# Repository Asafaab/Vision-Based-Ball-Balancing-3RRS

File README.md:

# Vision-Based Ball Balancing Using a 3-RRS Parallel Mechanism

### Mounted on a Differential-Drive Mobile Robot

<p align="center">
  <strong>
    Universidad de Ingeniería y Tecnología (UTEC)
  </strong>
  <br>
  Mechatronics Engineering | Diseño de Sistemas Mecatrónicos
</p>

---

## Digital and Physical Prototype

This project presents a vision-based ball-balancing
system that integrates a three-degree-of-freedom
3-RRS parallel mechanism with a differential-drive
mobile robotic platform.

<table>
<tr>
<th align="center">Digital Prototype</th>
<th align="center">Physical Prototype</th>
</tr>
<tr>
<td width="50%" align="center">

</td>
<td width="50%" align="center">

</td>
</tr>
<tr>
<td align="center">
<em>Autodesk Inventor CAD model</em>
</td>
<td align="center">
<em>Assembled laboratory prototype</em>
</td>
</tr>
</table>

<p align="center">
<b>
Mechanical Design | Computer Vision | Parallel Robotics |
Embedded Control | Power Electronics
</b>
</p>

---

## 1. Project Overview

The project combines a mobile robotic platform
with a **3-RRS Ball-and-Plate parallel mechanism**
designed to regulate the position of a ball
through controlled platform inclination.

The system integrates:

- Differential-drive mobile locomotion.
- A three-limb 3-RRS parallel mechanism.
- Vision-based ball-position estimation.
- A transparent acrylic balancing platform.
- Circular LED illumination.
- Camera-based visual feedback.
- Distributed processing and actuation.
- A dedicated power-distribution PCB.

The mechanical structure was designed and
assembled using Autodesk Inventor and
modular TETRIX components.

### Main Processing Units

**NI myRIO-1900**

- Mobile robot drive control.
- Encoder signal acquisition.
- Inclination measurement.
- Motor control and feedback.

**Raspberry Pi 5**

- Image acquisition and processing.
- Ball-position detection.
- Camera integration.
- Ball-and-Plate actuation.

The vision system uses an Arducam OV9281
global-shutter camera positioned below
the balancing platform.

---

## 2. System Architecture

The robotic platform consists of five
main functional subsystems.

| Subsystem | Description |
|---|---|
| Mobile Robot | Differential-drive TETRIX chassis |
| 3-RRS Mechanism | Parallel balancing platform |
| Vision System | Camera and LED illumination |
| Control System | NI myRIO-1900 and Raspberry Pi 5 |
| Power Distribution | Dedicated PCB and power branches |

### Mobile Robotic Platform

The mobile robot incorporates a modular
aluminum structure, two driven wheels,
and passive omnidirectional support wheels.

The platform provides mechanical support
for the balancing mechanism and its
associated electronics.

### 3-RRS Parallel Mechanism

The balancing mechanism consists of three
servo-actuated limbs connected to a movable
platform through passive links and
spherical joints.

Its configuration allows controlled
platform inclination in roll and pitch.

### Vision System

The vision subsystem incorporates:

- Arducam OV9281 camera module.
- Camera lens and optical filter.
- Camera mounting structure.
- Circular LED illumination.
- Transparent acrylic platform.

### Distributed Control

The NI myRIO-1900 manages the mobile robot
control functions, while the Raspberry Pi 5
handles image processing and balancing
mechanism actuation.

---

## 3. Mechanical Design and CAD Assembly

The mechanical system was developed using
**Autodesk Inventor Professional 2025**.

Native Inventor files and STEP models
are provided for mechanical inspection,
design modification, and interoperability.

### 3.1 Complete Robot Assembly

<p align="center">
<em>
Complete CAD assembly of the differential-drive
robot integrated with the 3-RRS Ball-and-Plate
mechanism.
</em>
</p>

### 3.2 Complete Robot Exploded View

<p align="center">
<em>
Exploded view illustrating the main mechanical
and electronic subsystems of the robotic platform.
</em>
</p>

The exploded assembly highlights:

- Upper structural platform.
- Mobile robot chassis.
- Drive motor assemblies.
- Wheel assemblies.
- Electronic modules.
- 3-RRS balancing mechanism.
- Mechanical supports and interfaces.

### 3.3 3-RRS Mechanism Exploded View

<p align="center">
<em>
Detailed exploded CAD representation of the 3-RRS
Ball-and-Plate mechanism with component
identification and bill of materials.
</em>
</p>

The mechanism includes:

- Transparent acrylic platform.
- Upper structural ring.
- LED ring and supports.
- Spherical joints.
- Passive links.
- Actuated arms.
- Three servomotors.
- Servo mounting structure.
- Camera and optical components.

---

## 4. Vision and LED Illumination System

The vision subsystem is integrated beneath
the transparent acrylic balancing platform.

The circular LED arrangement supports
illumination of the monitored area,
while the camera is mounted below
the platform for visual acquisition.

<p align="center">
<em>
Detailed CAD visualization of the LED ring
and camera optical assembly.
</em>
</p>

### Main Optical Components

| Component | Function |
|---|---|
| Transparent Acrylic Platform | Balancing surface and optical access |
| LED Ring | Illumination of the monitored region |
| Camera Module | Image acquisition |
| Lens Assembly | Optical image formation |
| Optical Filter | Optical filtering |
| Camera Support | Mechanical positioning |

The design includes a dedicated mechanical
arrangement for the camera and its optical
components.

---

## 5. Physical Prototype

The physical prototype was assembled using
a modular TETRIX aluminum chassis.

The balancing mechanism is mounted above
the mobile base, integrating the actuation
system, transparent platform, and
vision-related components.

### Prototype Photographs

<table>
<tr>
<td align="center" width="50%">

<br>
<b>Isometric Overview</b>
</td>
<td align="center" width="50%">

<br>
<b>Front View</b>
</td>
</tr>
<tr>
<td align="center">

<br>
<b>Side View</b>
</td>
<td align="center">

<br>
<b>Power-Switch Detail</b>
</td>
</tr>
</table>

These photographs document the mechanical
integration of the mobile base, balancing
mechanism, wheel assemblies, structural
supports, and electrical wiring.

**Note:** Some CAD configurations represent
design updates and may differ from the
photographed physical prototype.

---

## 6. Power-Distribution PCB

A dedicated power-distribution printed
circuit board was developed for the
robotic platform.

The PCB was designed using **KiCad 9**
and documented for fabrication using
the laboratory CNC manufacturing process.

### PCB 3D Visualization

<p align="center">
<em>
Three-dimensional CAD representation of
the power-distribution PCB.
</em>
</p>

### PCB Specifications

| Parameter | Specification |
|---|---|
| Design Software | KiCad 9 |
| PCB Dimensions | 66.1 x 57.9 mm |
| Board Type | Single-sided |
| Input Supply | 12 V |
| Fabrication | Laboratory CNC |
| Main Function | Power distribution and protection |

The electrical architecture includes
reverse-polarity protection, transient
protection, fused distribution branches,
and auxiliary power connections.

### PCB Design Resources

| Resource | Repository |
|---|---|
| KiCad Source Files | [View files](Power_Distribution_PCB/kicad/) |
| PCB Manufacturing Files | [View files](Power_Distribution_PCB/cnc_L414/) |
| PCB 3D CAD Model | [View files](Power_Distribution_PCB/cad3d/) |
| Electrical Diagrams | [View files](Power_Distribution_PCB/diagramas/) |
| PCB Images | [View files](Power_Distribution_PCB/imagenes/) |
| Thermal Analysis | [View files](Power_Distribution_PCB/termico/) |
| Technical Report | [View PDF](Power_Distribution_PCB/Anexo2_PCB_PDE-DSM_v1.pdf) |
| Pinout and Connections | [View document](Power_Distribution_PCB/Conexiones_y_pines.md) |
| Verification Report | [View document](Power_Distribution_PCB/Informe_verificacion.md) |

For detailed manufacturing requirements
and electrical specifications, consult
the original PCB design documentation.

---

## 7. Engineering Design Resources

The repository provides source files
and technical resources for inspecting,
reproducing, and modifying the platform.

| Design Resource | Format | Repository |
|---|---|---|
| Complete Robot Assembly | STEP | [View](Mechanical_Design/Complete_Robot/Complete_Robot_Assembly.stp) |
| 3-RRS Mechanism | STEP | [View](Mechanical_Design/Complete_Robot/3RRS_Mechanism.stp) |
| Original CAD Package | ZIP | [View](Mechanical_Design/Complete_Robot/Ensamblaje1.zip) |
| Native Inventor Assembly | IAM, IPT, IPJ | [View](Inventor_Source_Files/) |
| Mechanical Drawings | CAD, PDF | [View](Engineering_Drawings/) |
| Kinematic Analysis | MATLAB | [View](Kinematic_Analysis/) |
| CAD Visualizations | PNG | [View](CAD_Visualizations/) |
| Physical Prototype | JPG | [View](Physical_Prototype_Photos/) |
| PCB Design | KiCad, Gerber, STEP | [View](Power_Distribution_PCB/) |

---

## 8. Repository Structure

    Vision-Based-Ball-Balancing-3RRS/
    |
    |-- Mechanical_Design/
    |   `-- Complete_Robot/
    |       |-- Complete_Robot_Assembly.stp
    |       |-- 3RRS_Mechanism.stp
    |       |-- Ensamblaje1.zip
    |       `-- README.md
    |
    |-- Inventor_Source_Files/
    |   |-- DSM_CAD_REPARADO.ipj
    |   |-- Ensamblaje1.iam
    |   |-- Piezas/
    |   |-- Dependencias/
    |   `-- _Verificacion/
    |
    |-- CAD_Visualizations/
    |   |-- Full_Robot_Assembly.png
    |   |-- Full_Robot_Exploded_View.png
    |   |-- 3RRS_Mechanism_Exploded_View.png
    |   |-- Camera_and_LED_System.png
    |   `-- Additional CAD images
    |
    |-- Physical_Prototype_Photos/
    |   `-- Prototype photographs
    |
    |-- Power_Distribution_PCB/
    |   |-- kicad/
    |   |-- cnc_L414/
    |   |-- cad3d/
    |   |-- diagramas/
    |   |-- imagenes/
    |   |-- termico/
    |   `-- Technical documentation
    |
    |-- Engineering_Drawings/
    |   `-- Planos.zip
    |
    |-- Kinematic_Analysis/
    |   `-- Cinemática_RSS.m.txt
    |
    |-- README.md
    `-- LICENSE

---

## 9. Opening the Autodesk Inventor Project

**Required CAD Software:**
Autodesk Inventor Professional 2025.

### Instructions

1. Clone or download the complete repository.
2. Preserve the original directory structure.
3. Open Autodesk Inventor Professional 2025.
4. Activate the project file:

   `Inventor_Source_Files/DSM_CAD_REPARADO.ipj`

5. Open the main assembly:

   `Inventor_Source_Files/Ensamblaje1.iam`

6. Allow Inventor to resolve the referenced
   components and dependencies.
7. Verify the assembly structure and
   mechanical constraints.

The source project includes native Inventor
parts, subassemblies, and supporting
verification records.

### Verification Resources

The verification files are located in:

[Inventor Assembly Verification](Inventor_Source_Files/_Verificacion/)

These records document previous assembly
and reference checks. Users should also
verify the assembly in their local
CAD environment.

---

## 10. Kinematic Analysis

The 3-RRS parallel mechanism is supported
by a MATLAB-based inverse-kinematics model.

The analysis relates the desired platform
orientation to the actuator configuration
through the geometry of the parallel
mechanism.

**Source files:**

[Kinematic Analysis](Kinematic_Analysis/)

The currently published source uses
the `.m.txt` filename extension.

For MATLAB execution, a working copy
can be saved using the `.m` extension.

---

## 11. Design Reproduction Guidelines

For mechanical and electronic reproduction:

1. Review the available CAD models.
2. Inspect the engineering drawings.
3. Verify dimensions and component materials.
4. Check actuator operating limits.
5. Verify mechanical clearances.
6. Inspect the PCB connection diagrams.
7. Review electrical protection requirements.
8. Validate the assembly before operation.

CAD visualizations represent the
documented design configurations.

Physical prototype photographs document
the hardware arrangement shown at the
time of acquisition.

---

## 12. Original Project and Acknowledgments

The 3-RRS Ball-and-Plate mechanism was adapted
from the open-source Ball-Balancing-Robot
project developed by **I-M-Robotics-Lab**.

Original repository:

[Ball-Balancing-Robot — I-M-Robotics-Lab](https://github.com/I-M-Robotics-Lab/Ball-Balancing-Robot)

The present work integrates the mechanism
with a differential-drive mobile robot,
vision hardware, distributed control,
and a dedicated power-distribution PCB.

The original design attribution and
applicable licensing conditions are preserved.

---

## 13. License

This repository includes the
**GNU General Public License v3.0**.

See the [LICENSE](LICENSE) file
for the complete license text.

Third-party components and reused
resources remain subject to their
respective licensing and attribution
requirements.

---

## 14. Project Information

**Project Title:**

Vision-Based Ball Balancing Using a 3-RRS
Parallel Mechanism Mounted on a
Differential-Drive Mobile Robot.

**Institution:**
Universidad de Ingeniería y Tecnología (UTEC).

**Location:**
Lima, Peru.

**Course:**
Diseño de Sistemas Mecatrónicos (DSM).

**Mechanical CAD:**
Autodesk Inventor Professional 2025.

**Electronic Design:**
KiCad 9.

**Engineering Analysis:**
MATLAB.

**Computing Platforms:**
NI myRIO-1900 and Raspberry Pi 5.

**Repository Contents:**
Mechanical CAD, PCB design, engineering
drawings, kinematic analysis, CAD visualizations,
and physical prototype documentation.

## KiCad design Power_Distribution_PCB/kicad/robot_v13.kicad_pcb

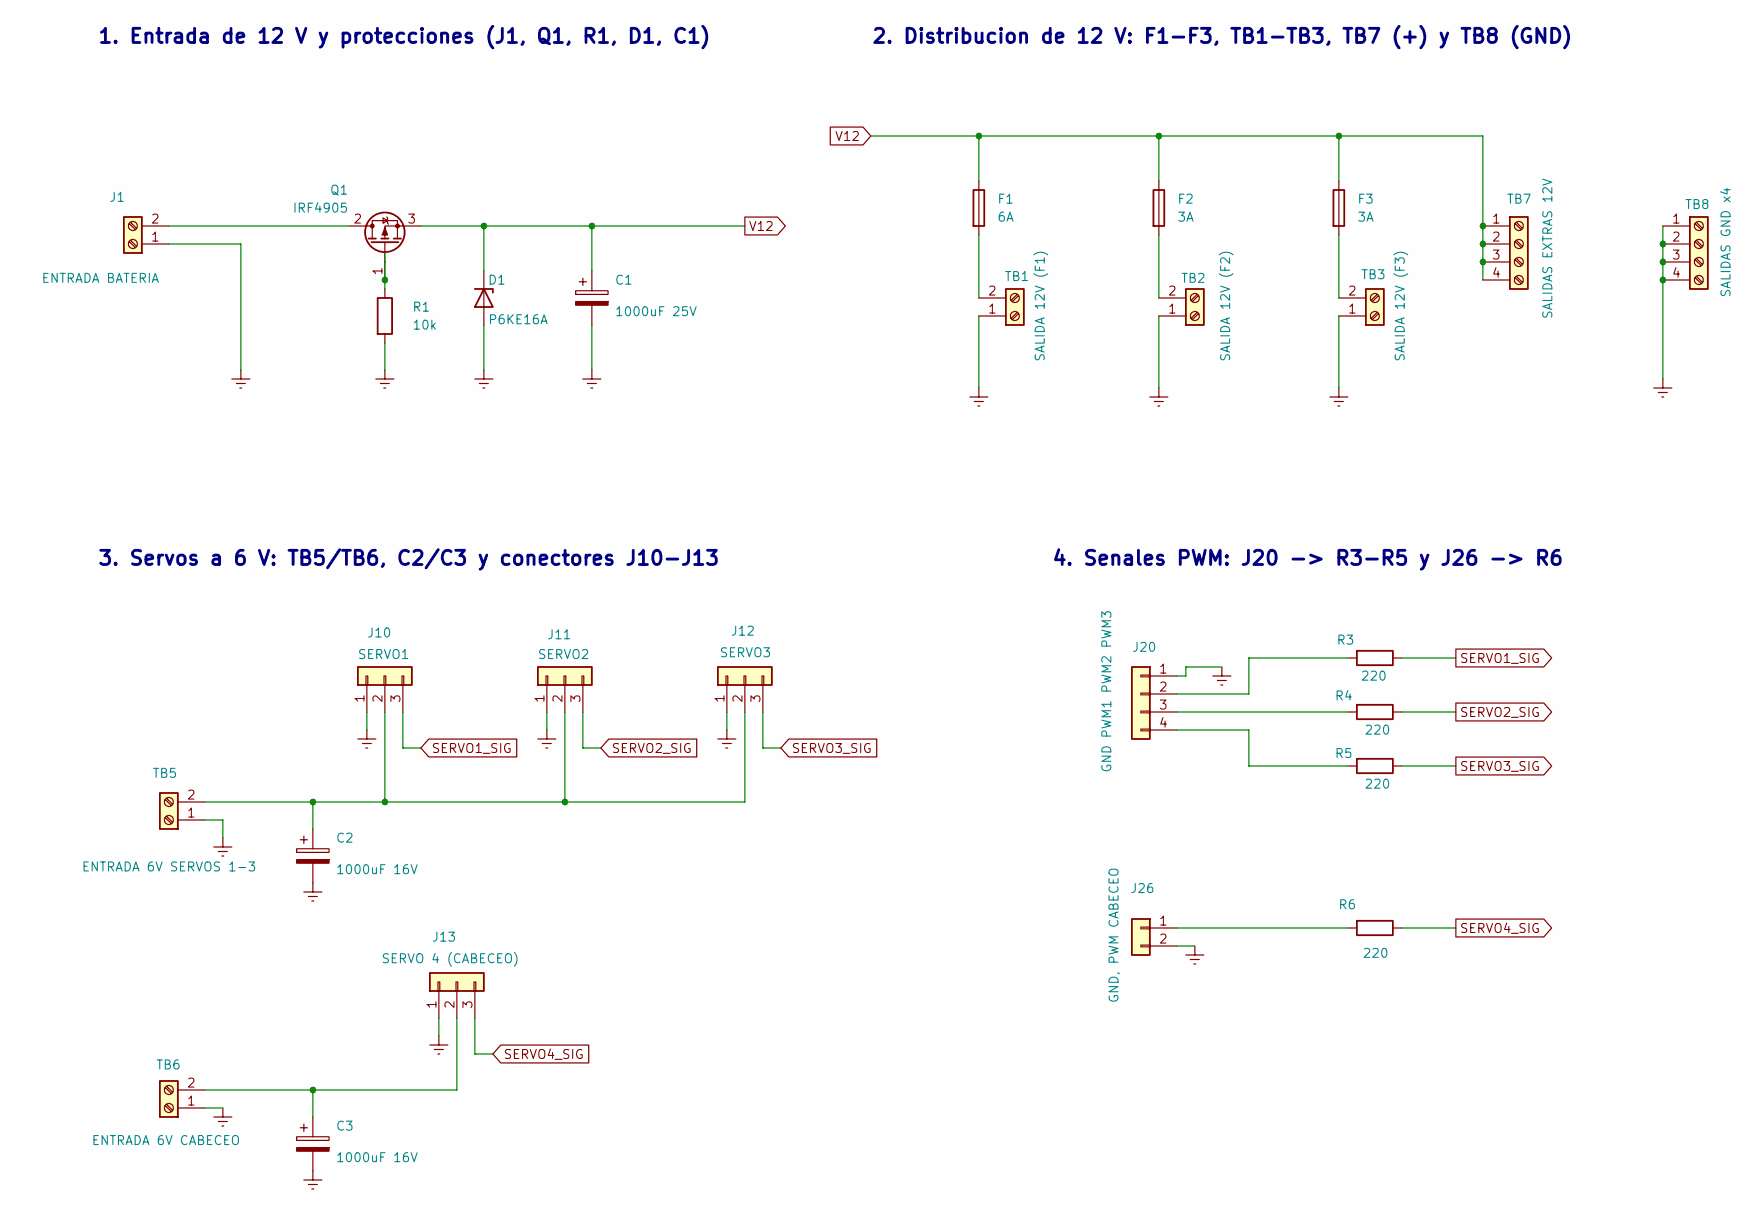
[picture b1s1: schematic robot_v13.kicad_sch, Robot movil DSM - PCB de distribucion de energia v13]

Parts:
C1: 1000uF 25V; CP_Radial_D10.0mm_P5.00mm
C2, C3: 1000uF 16V; CP_Radial_D10.0mm_P5.00mm
D1: P6KE16A; D_DO-15_P10.16mm_Horizontal
F1: 6A; Fuseholder_Clip-5x20mm_Littelfuse_111_Inline_P20.00x5.00mm_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
F2, F3: 3A; Fuseholder_Clip-5x20mm_Littelfuse_111_Inline_P20.00x5.00mm_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
J1: ENTRADA BATERIA; TerminalBlock_Phoenix_MKDS-1,5-2-5.08_1x02_P5.08mm_Horizont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
J10: SERVO1; PinHeader_1x03_P2.54mm_Vertical
J11: SERVO2; PinHeader_1x03_P2.54mm_Vertical
J12: SERVO3; PinHeader_1x03_P2.54mm_Vertical
J13: SERVO 4 (CABECEO); PinHeader_1x03_P2.54mm_Vertical
J20: GND PWM1 PWM2 PWM3; PinHeader_1x04_P2.54mm_Vertical
J26: GND, PWM CABECEO; PinHeader_1x02_P2.54mm_Vertical
Q1: IRF4905; TO-220-3_Vertical
R1: 10k; R_Axial_DIN0207_L6.3mm_D2.5mm_P7.62mm_Horizontal
R3, R4, R5, R6: 220; R_Axial_DIN0207_L6.3mm_D2.5mm_P7.62mm_Horizontal
TB1: SALIDA 12V (F1); TerminalBlock_Phoenix_MKDS-1,5-2-5.08_1x02_P5.08mm_Horizont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
TB2: SALIDA 12V (F2); TerminalBlock_Phoenix_MKDS-1,5-2-5.08_1x02_P5.08mm_Horizont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
TB3: SALIDA 12V (F3); TerminalBlock_Phoenix_MKDS-1,5-2-5.08_1x02_P5.08mm_Horizont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
TB5: ENTRADA 6V SERVOS 1-3; TerminalBlock_Phoenix_MKDS-1,5-2-5.08_1x02_P5.08mm_Horizont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
TB6: ENTRADA 6V CABECEO; TerminalBlock_Phoenix_MKDS-1,5-2-5.08_1x02_P5.08mm_Horizont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
TB7: SALIDAS EXTRAS 12V; TerminalBlock_Phoenix_MKDS-1,5-4-5.08_1x04_P5.08mm_Horizont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
TB8: SALIDAS GND x4; TerminalBlock_Phoenix_MKDS-1,5-4-5.08_1x04_P5.08mm_Horizont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

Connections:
GND: C1.2, C2.2, C3.2, D1.2 (A), J1.1, J10.1, J11.1, J12.1, J13.1, J20.1, J26.2, R1.2, TB1.1, TB2.1, TB3.1, TB5.1, TB6.1, TB8.1, TB8.2, TB8.3, TB8.4
unnamed: J1.2, Q1.2 (D)
unnamed: C2.1, J10.2, J11.2, J12.2, TB5.2
unnamed: C3.1, J13.2, TB6.2
unnamed: J20.2, R3.2
unnamed: J20.3, R4.2
unnamed: J20.4, R5.2
unnamed: J26.1, R6.2
unnamed: Q1.1 (G), R1.1
unnamed: F1.2, TB1.2
unnamed: F2.2, TB2.2
unnamed: F3.2, TB3.2
SERVO1_SIG: J10.3, R3.1
SERVO2_SIG: J11.3, R4.1
SERVO3_SIG: J12.3, R5.1
SERVO4_SIG: J13.3, R6.1
V12: C1.1, D1.1 (K), F1.1, F2.1, F3.1, Q1.3 (S), TB7.1, TB7.2, TB7.3, TB7.4

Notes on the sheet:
1. Entrada de 12 V y protecciones (J1, Q1, R1, D1, C1)
4. Senales PWM: J20 -> R3-R5 y J26 -> R6
3. Servos a 6 V: TB5/TB6, C2/C3 y conectores J10-J13
2. Distribucion de 12 V: F1-F3, TB1-TB3, TB7 (+) y TB8 (GND)

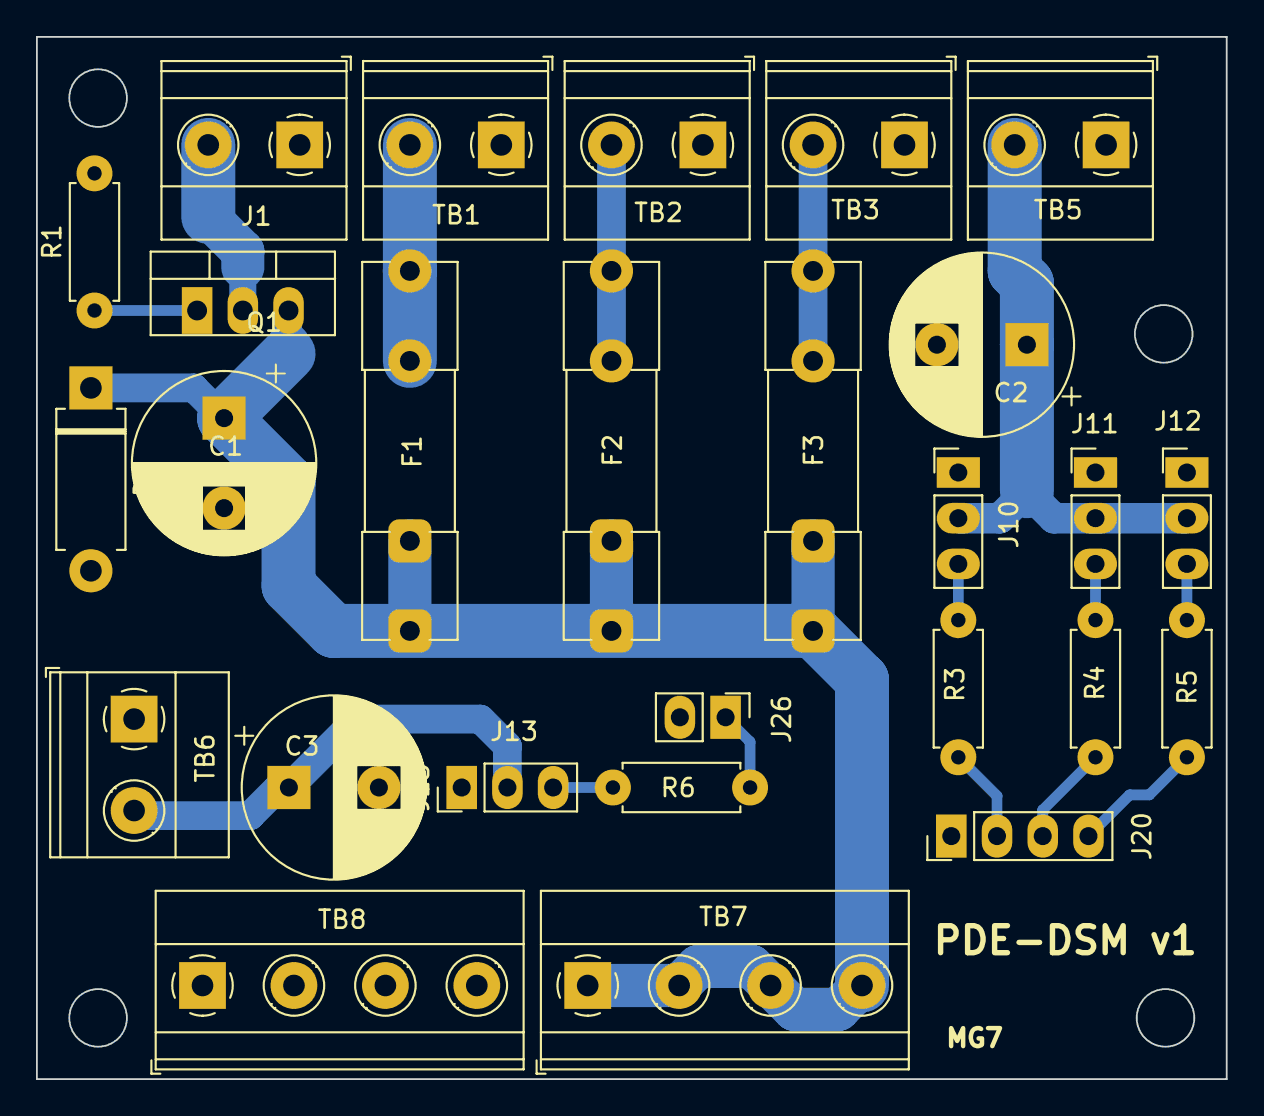
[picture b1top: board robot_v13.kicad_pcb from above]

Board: 2 copper layers, 66.1 x 57.9 mm, 27 parts (0 on the bottom side), 17 nets.

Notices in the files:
README.md:
License: GPL-3.0
